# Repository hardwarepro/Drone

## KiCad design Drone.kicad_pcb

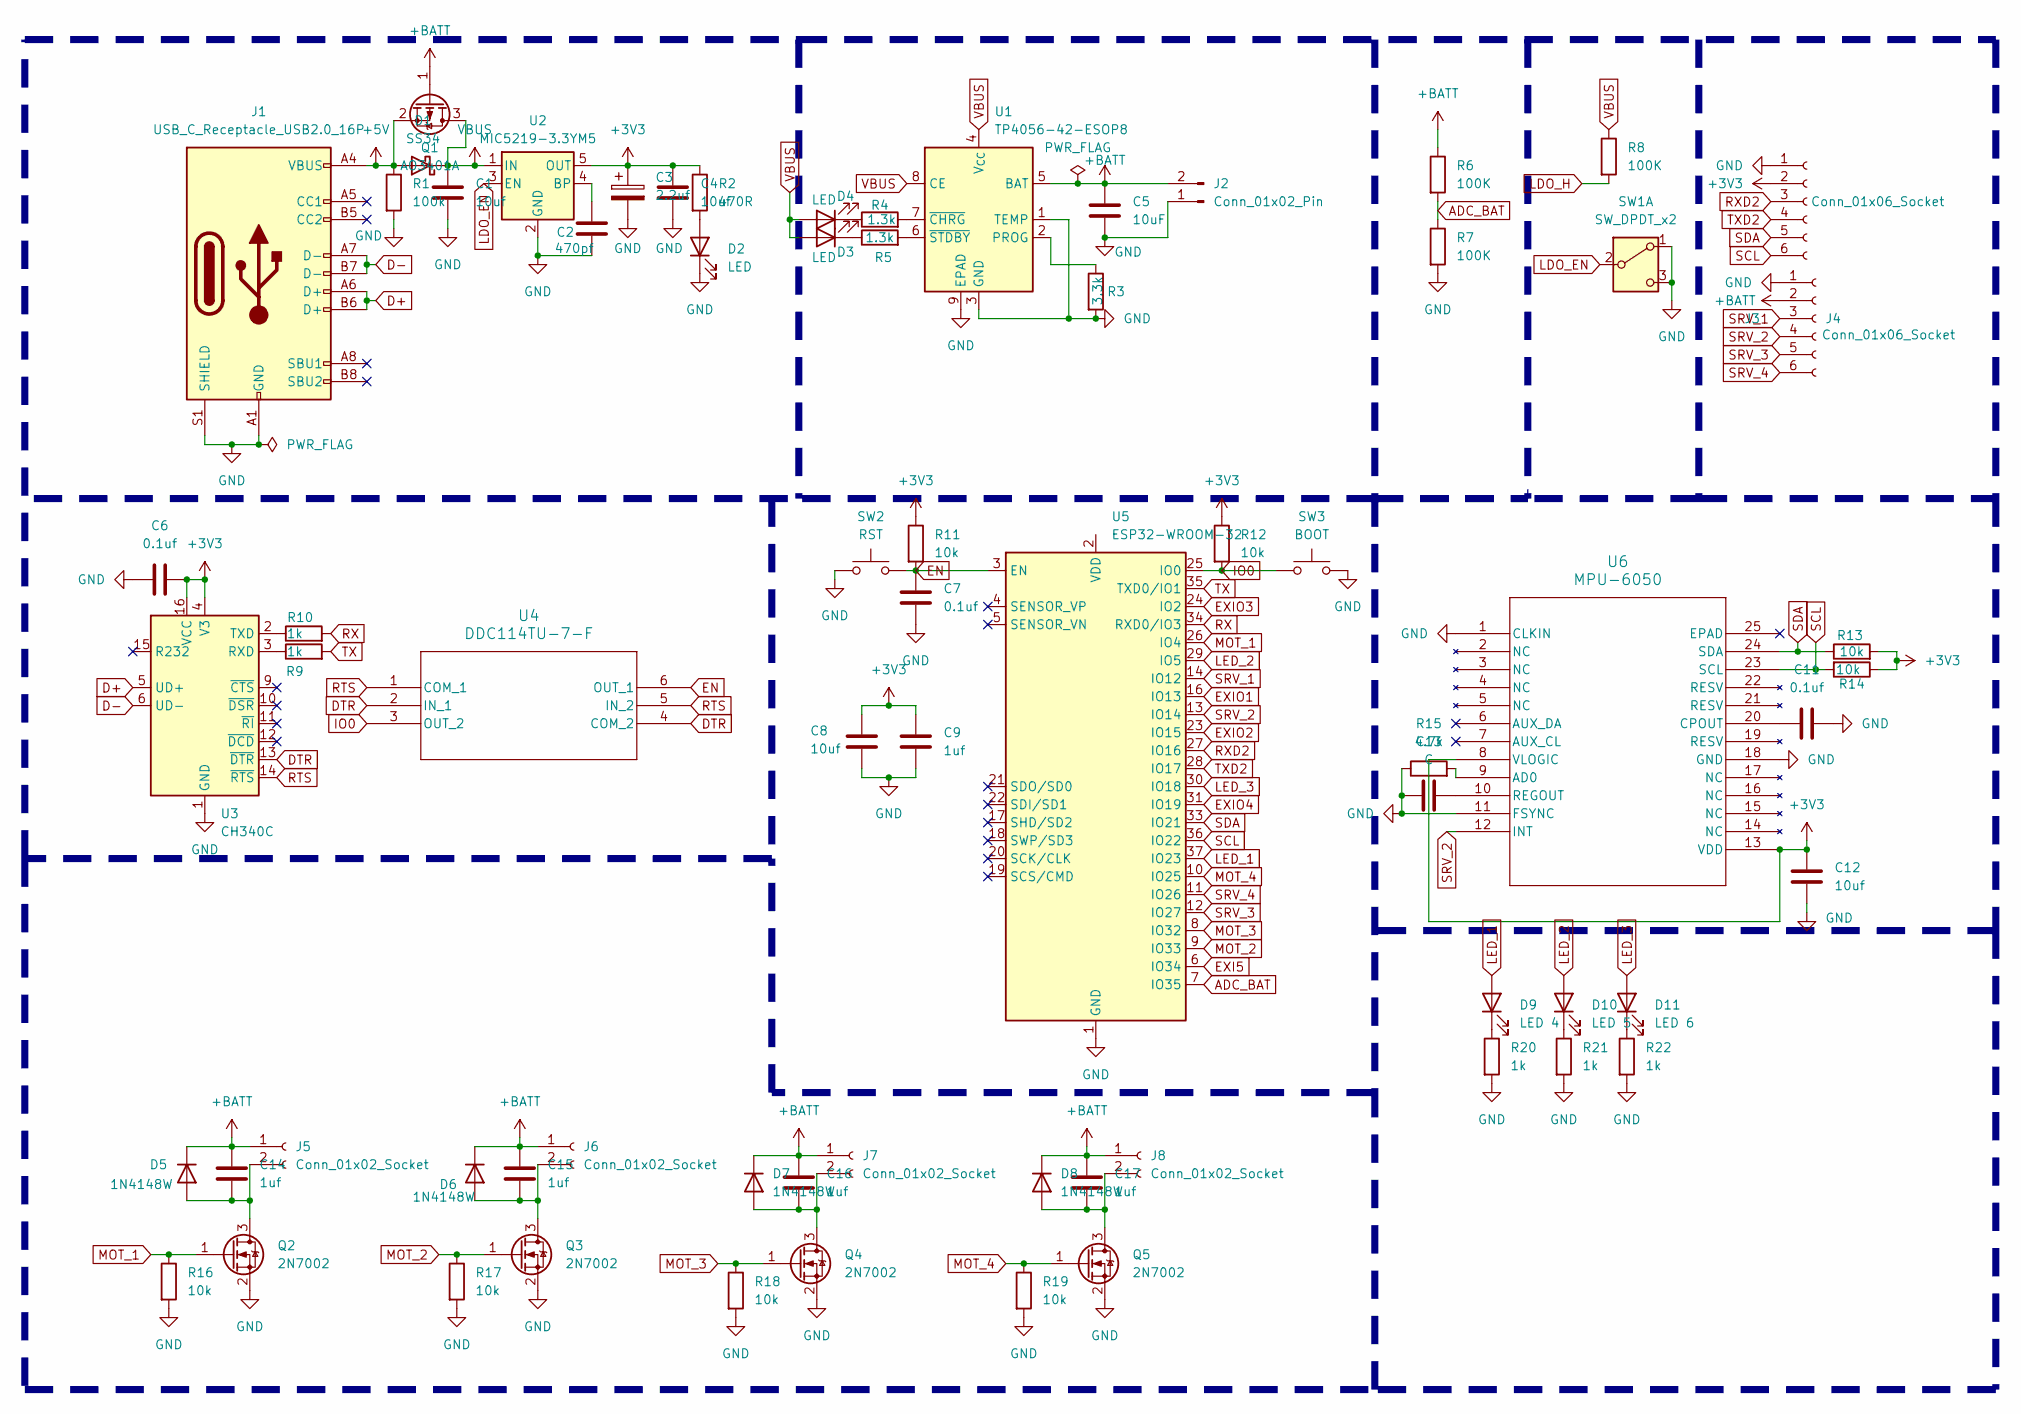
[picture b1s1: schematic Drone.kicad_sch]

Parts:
C1, C4, C8, C12: 10uf; C_0603_1608Metric
C2: 470pf; C_0603_1608Metric
C3: 2.2uf; C_0603_1608Metric
C5: 10uF; C_0603_1608Metric
C6, C7, C11: 0.1uf; C_0603_1608Metric
C9, C14, C15, C16, C17: 1uf; C_0603_1608Metric
C13: C; C_0603_1608Metric
D1: SS34; D_0603_1608Metric
D2, D3, D4: LED; LED_0603_1608Metric
D5, D6, D7, D8: 1N4148W; D_SOD-123
D9: LED 4; LED_0603_1608Metric
D10: LED 5; LED_0603_1608Metric
D11: LED 6; LED_0603_1608Metric
J1: USB_C_Receptacle_USB2.0_16P; USB_C_Receptacle_HCTL_HC-TYPE-C-16P-01A
J2: Conn_01x02_Pin; PinHeader_1x02_P2.54mm_Vertical
J3, J4: Conn_01x06_Socket; PinHeader_1x06_P2.54mm_Vertical
J5, J6, J7, J8: Conn_01x02_Socket; PinHeader_1x02_P2.54mm_Vertical
Q1: AO3401A; SOT-23
Q2, Q3, Q4, Q5: 2N7002; SOT-23
R1: 100k; R_0603_1608Metric
R2: 470R; R_0603_1608Metric
R3: 3.3k; R_0603_1608Metric
R4, R5: 1.3k; R_0603_1608Metric
R6, R7, R8: 100K; R_0603_1608Metric
R9, R10, R20, R21, R22: 1k; R_0603_1608Metric
R11, R12, R13, R14, R16, R17, R18, R19: 10k; R_0603_1608Metric
R15: 4.7k; R_0603_1608Metric
SW1: SW_DPDT_x2; SW_PUSH_6mm
SW2: RST; SW_PUSH_6mm
SW3: BOOT; SW_PUSH_6mm
U1: TP4056-42-ESOP8; SOIC-8-1EP_3.9x4.9mm_P1.27mm_EP2.41x3.3mm_ThermalVias
U2: MIC5219-3.3YM5; SOT-23-5
U3: CH340C; SOIC-16_3.9x9.9mm_P1.27mm
U4: DDC114TU-7-F; SOT_363_DIO
U5: ESP32-WROOM-32
U6: MPU-6050; QFN24_4X4X0P9-0P5_TDK

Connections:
+3V3: C3.1, C4.1, C6.2, C8.1, C9.1, C12.1, J3.2, R2.1, R11.1, R12.1, R13.2, R14.1, U2.5 (OUT), U3.4 (V3), U3.16 (VCC), U6.8 (VLOGIC), U6.13 (VDD)
+5V: D1.2 (A), J1.A4 (VBUS), J1.A9 (VBUS), J1.B4 (VBUS), J1.B9 (VBUS), Q1.2 (S), R1.1
+BATT: C5.1, C14.1, C15.1, C16.1, C17.1, D5.1 (K), D6.1 (K), D7.1 (K), D8.1 (K), J2.2, J4.2, J5.1, J6.1, J7.1, J8.1, Q1.1 (G), R6.1, U1.5 (BAT)
ADC_BAT: R6.2, R7.1, U5.7 (IO35)
D+: J1.A6 (D+), J1.B6 (D+), U3.5 (UD+)
D-: J1.A7 (D-), J1.B7 (D-), U3.6 (UD-)
DTR: U3.13 (~DTR), U4.2 (IN_1), U4.4 (COM_2)
EN: C7.2, R11.2, SW2.2, U4.6 (OUT_1), U5.3 (EN)
EXI5: U5.6 (IO34)
EXIO1: U5.16 (IO13)
EXIO2: U5.23 (IO15)
EXIO3: U5.24 (IO2)
EXIO4: U5.31 (IO19)
GND: C1.2, C2.2, C3.2, C4.2, C5.2, C6.1, C7.1, C8.2, C9.2, C11.2, C12.2, C13.1, D2.1 (K), J1.A1 (GND), J1.A12 (GND), J1.B1 (GND), J1.B12 (GND), J1.S1 (SHIELD), J2.1, J3.1, J4.1, Q2.2 (S), Q3.2 (S), Q4.2 (S), Q5.2 (S), R1.2, R3.2, R7.2, R15.1, R16.2, R17.2, R18.2, R19.2, R20.2, R21.2, R22.2, SW1.1 (A), SW1.3 (C), SW2.1, SW3.2, U1.1 (TEMP), U1.3 (GND), U1.9 (EPAD), U2.2 (GND), U3.1 (GND), U5.1 (GND), U5.15 (GND), U5.38 (GND), U5.39 (GND), U6.1 (CLKIN), U6.11 (FSYNC), U6.18 (GND)
IO0: R12.2, SW3.1, U4.3 (OUT_2), U5.25 (IO0)
LDO_EN: SW1.2 (B), U2.3 (EN)
LDO_H: R8.2
LED_1: D9.2 (A), U5.37 (IO23)
LED_2: D10.2 (A), U5.29 (IO5)
LED_3: D11.2 (A), U5.30 (IO18)
MOT_1: Q2.1 (G), R16.1, U5.26 (IO4)
MOT_2: Q3.1 (G), R17.1, U5.9 (IO33)
MOT_3: Q4.1 (G), R18.1, U5.8 (IO32)
MOT_4: Q5.1 (G), R19.1, U5.10 (IO25)
unnamed: D2.2 (A), R2.2
unnamed: D3.1 (K), R5.1
unnamed: D4.1 (K), R4.1
unnamed: C14.2, D5.2 (A), J5.2, Q2.3 (D)
unnamed: C15.2, D6.2 (A), J6.2, Q3.3 (D)
unnamed: C16.2, D7.2 (A), J7.2, Q4.3 (D)
unnamed: C17.2, D8.2 (A), J8.2, Q5.3 (D)
unnamed: D9.1 (K), R20.1
unnamed: D10.1 (K), R21.1
unnamed: D11.1 (K), R22.1
unnamed: R3.1, U1.2 (PROG)
unnamed: R4.2, U1.7 (~CHRG)
unnamed: R5.2, U1.6 (~STDBY)
unnamed: C2.1, U2.4 (BP)
unnamed: R9.1, U3.3 (RXD)
unnamed: R10.1, U3.2 (TXD)
unnamed: R15.2, U6.9 (AD0)
unnamed: C11.1, U6.20 (CPOUT)
unnamed: C13.2, U6.10 (REGOUT)
RTS: U3.14 (~RTS), U4.1 (COM_1), U4.5 (IN_2)
RX: R10.2, U5.34 (RXD0/IO3)
RXD2: J3.3, U5.27 (IO16)
SCL: J3.6, R14.2, U5.36 (IO22), U6.23 (SCL)
SDA: J3.5, R13.1, U5.33 (IO21), U6.24 (SDA)
SRV_1: J4.3, U5.14 (IO12)
SRV_2: J4.4, U5.13 (IO14), U6.12 (INT)
SRV_3: J4.5, U5.12 (IO27)
SRV_4: J4.6, U5.11 (IO26)
TX: R9.2, U5.35 (TXD0/IO1)
TXD2: J3.4, U5.28 (IO17)
VBUS: C1.1, D1.1 (K), D3.2 (A), D4.2 (A), Q1.3 (D), R8.1, U1.4 (V_{CC}), U1.8 (CE), U2.1 (IN)

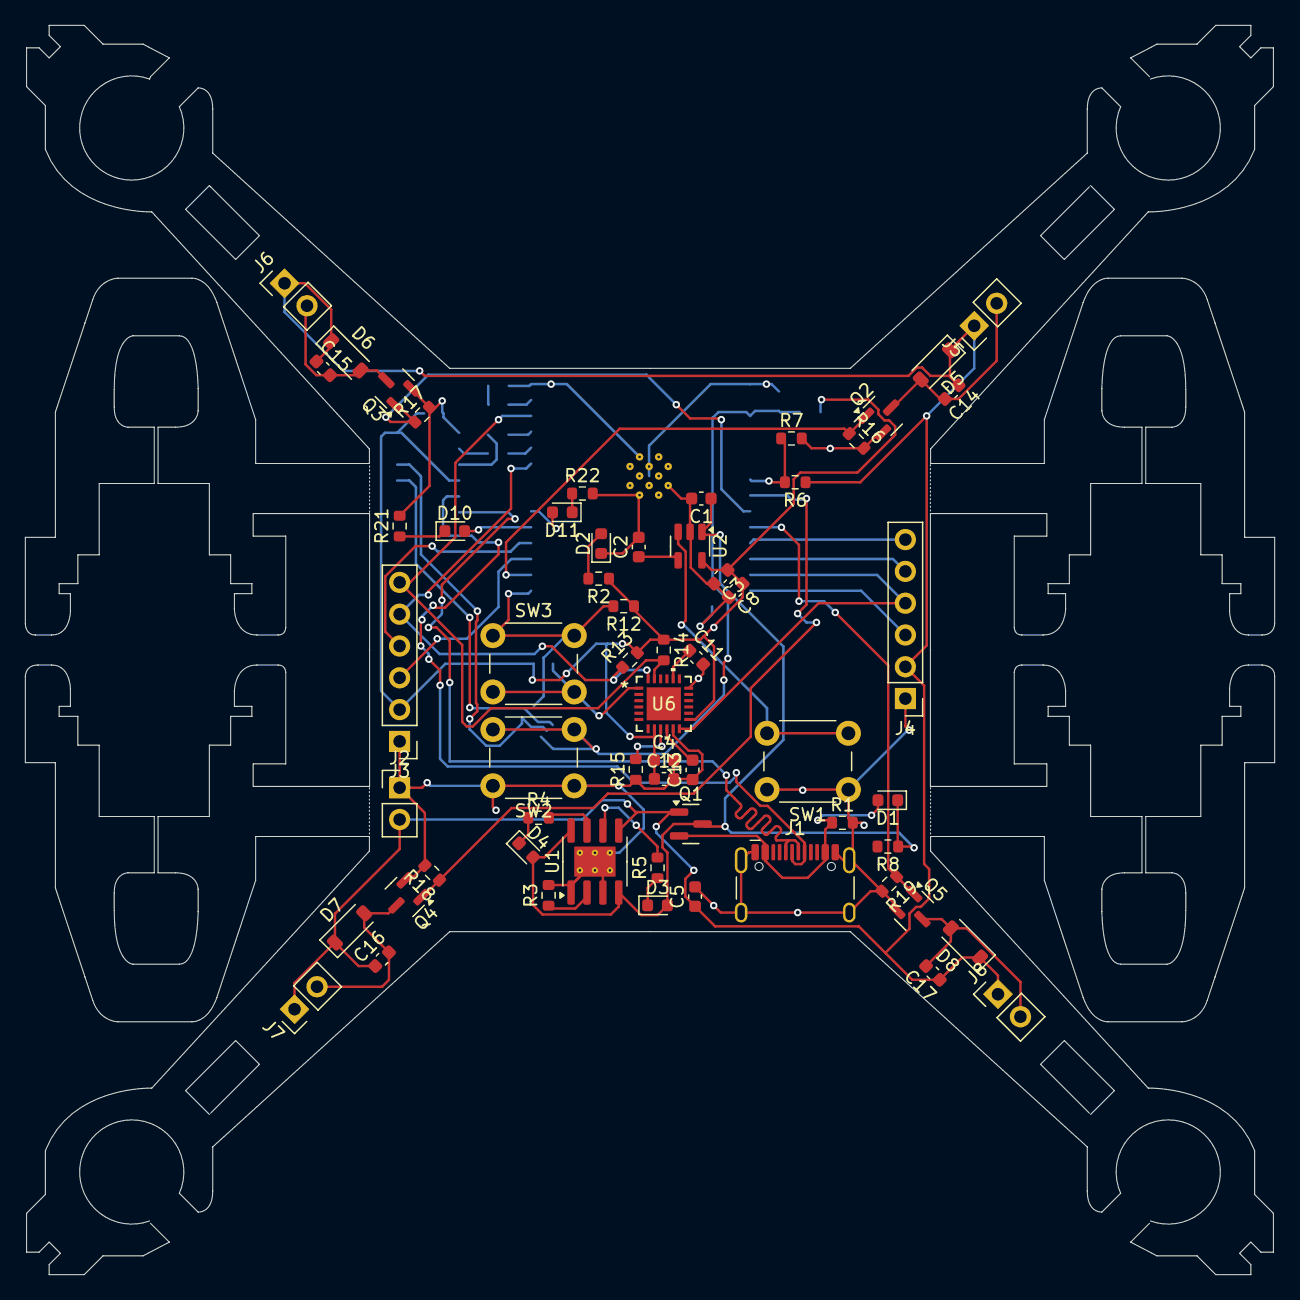
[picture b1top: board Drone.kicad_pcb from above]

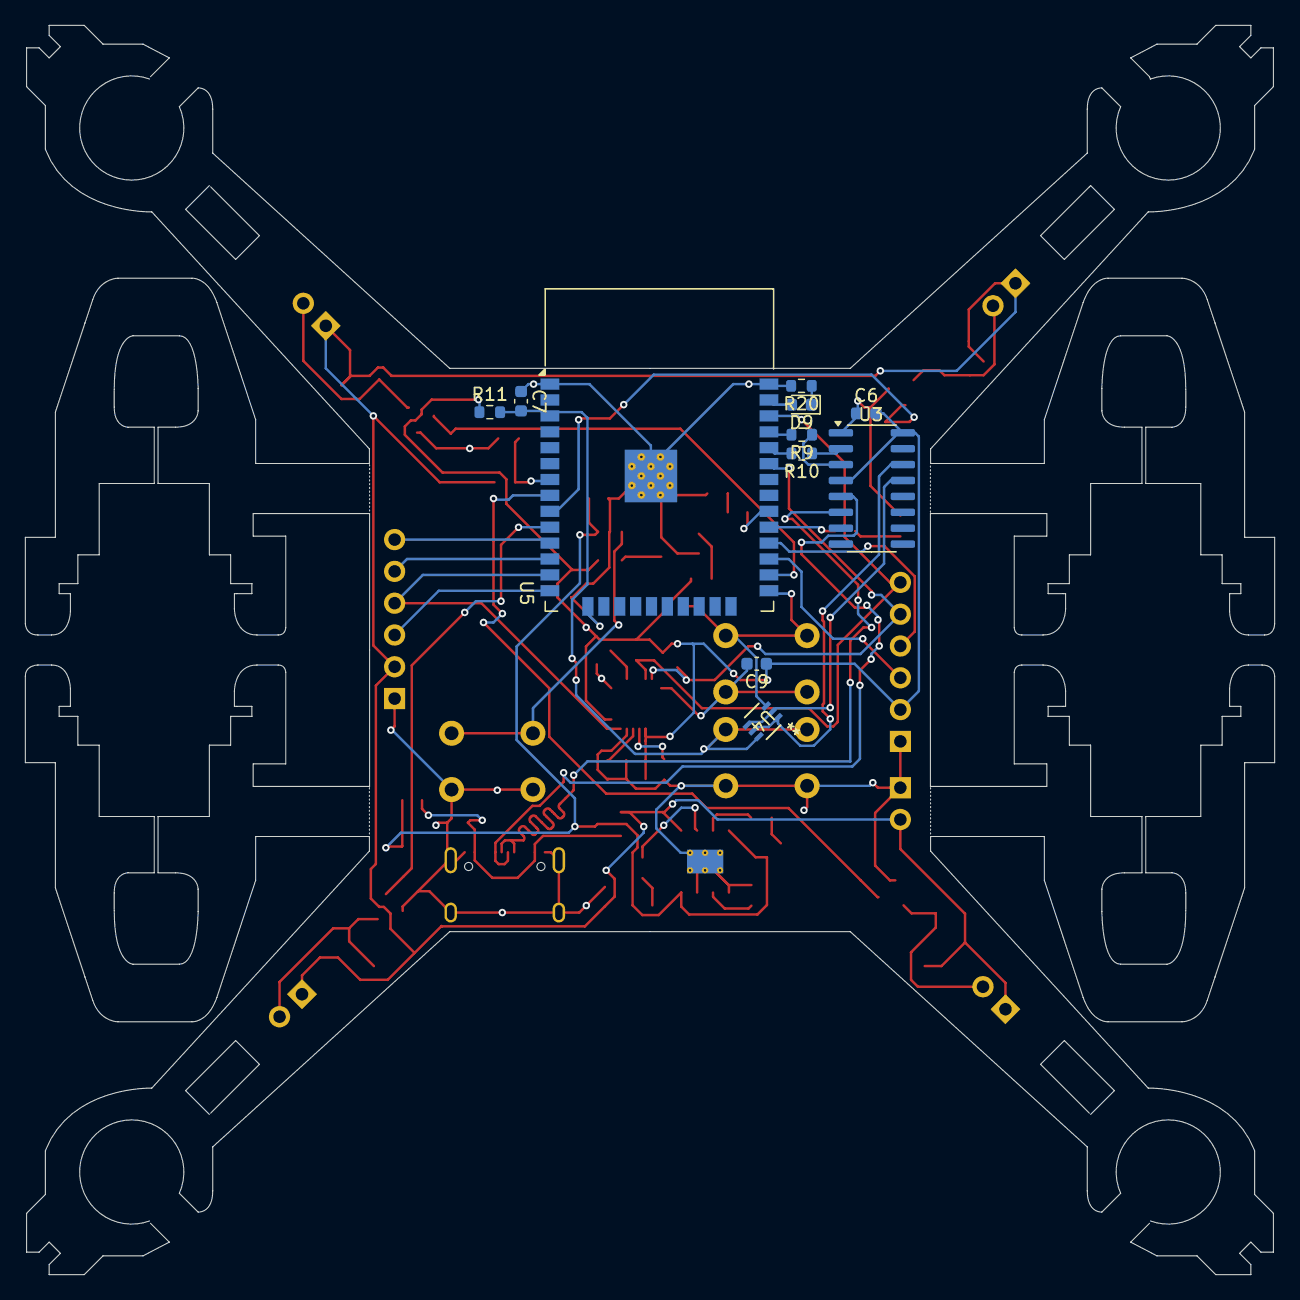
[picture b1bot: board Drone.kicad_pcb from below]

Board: 2 copper layers, 99.8 x 99.8 mm, 71 parts (11 on the bottom side), 49 nets.

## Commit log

2025-10-28 Initial commit: schematic done
2025-10-28 added n channel mosfets
2025-11-02 done outine
    Starting PCB outline
2025-11-07 V1 of PCB
